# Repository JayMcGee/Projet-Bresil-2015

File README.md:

Projet-Bresil-2015
==================

Projet TSO, Créer une balise avec des capteurs de qualité de l'eau pour l'université de Porto Allegre

http://www.bonebrews.com/temperature-monitoring-with-the-ds18b20-on-a-beaglebone-black/

https://github.com/jlucidar/FabMo-Platform/tree/master/Arch_linux_config/rtl8188CUS-driver-beaglebone

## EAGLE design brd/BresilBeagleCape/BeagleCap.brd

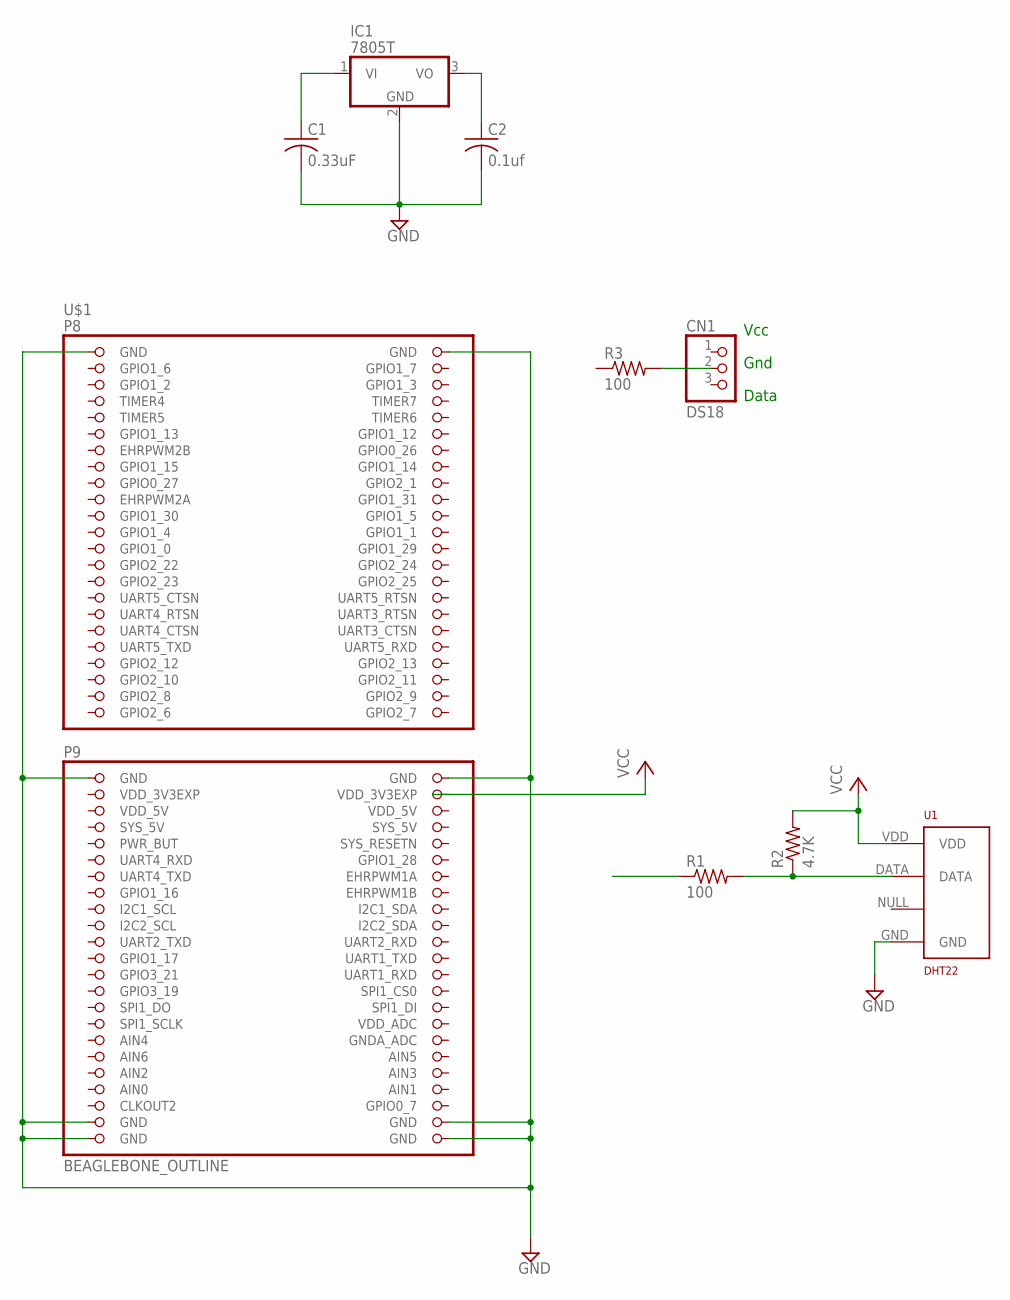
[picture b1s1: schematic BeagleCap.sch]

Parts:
C1: 0.33uF; C050-024X044
C2: 0.1uf; C050-024X044
CN1: DS18; JSTPH3
IC1: 7805T; TO220H
R1, R3: 100; 0207/10
R2: 4.7K; 0207/10
U1: DHT22; RHT03_DHT-22/RA
U$1: BEAGLEBONE_OUTLINE; BEAGLEBONE_SHIELD

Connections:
AIN0: U$1.85 (AIN0)
GND: C1.2, C2.2, IC1.2 (GND), U1.GND, U$1.1 (GND), U$1.2 (GND), U$1.47 (GND), U$1.48 (GND), U$1.89 (GND), U$1.90 (GND), U$1.91 (GND), U$1.92 (GND)
unnamed: C1.1, IC1.1 (VI)
unnamed: C2.1, IC1.3 (VO)
unnamed: R1.2, R2.1, U1.DATA
unnamed: CN1.2, R3.2
SYS_5V: U$1.53 (SYS_5V)
VCC: R2.2, U1.VDD
VDD_3V3EXP: U$1.49 (VDD_3V3EXP), U$1.50 (VDD_3V3EXP)
VDD_5V: U$1.51 (VDD_5V), U$1.52 (VDD_5V)

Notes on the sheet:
Vcc
Gnd
Data

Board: 2 copper layers, 9 parts (0 on the bottom side), 8 nets, no tracks yet.

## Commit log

2014-10-01 Example de MultiThreading pour le beaglebone
2014-10-01 Ajout de tout ce qui était dans mon fork
2014-10-01 Deplacement de la librairie à un endroit désigné
2014-10-01 Ajout des codes et exemples des années précédentes
2014-10-02 Mise a jour du code pour le PIC32MZ, code crée en parallèle avec l'avancement du BeagleBone pour le cas d'un plan de backup
2014-10-02 Ajout du code des annees précédentes
2014-10-02 Corrections pour que ca fonctionne
2014-10-02 Ajout de documentation pour l'installation de l'IDE pour le BeagleBone
2014-10-03 Trie des documentations et suppression de fichiers superflus (ex: Arduino 1.0.4 IDE)
2014-10-03 Modifications pour compatibilité
2014-10-04 Ajout de notes suite a la lecture de la documentation (manuels technoques) des années précédentes et d'un exemple de JSON en provenance du Drive de Mathieu
2014-10-05 Ajout d'un première version de l'installation de Cloud9 IDE sur le beaglebone/Ubuntu sans erreur et fonctionnement comme voulu
2014-10-05 Mise a jour apres test, la procédure est fonctionnelle sur Ubuntu 14.04 64bit
2014-10-08 Ajout de la méthode d'activation de UART5
2014-10-08 Ajout de source pour DHT22
2014-10-08 Ajout de code de base pour le DHt22
2014-10-13 Ajout d'une librairie de test pour le one wire
2014-10-13 Correction, voila la libraire correctment mise a sa place
2014-10-17 Suppression de la doc pour aller dans le Drive
2014-10-18 Ajout du readme que j'ai supprimé + lien vers device tree
2014-10-19 Added OneWire device class files, makes reading OneWire device in device tree easier.
    Follow this tutorial to create device tree :
    http://www.bonebrews.com/temperature-monitoring-with-the-ds18b20-on-a-beaglebone-black/
2014-10-19 Skeleton classe for UART operated devices. Example based on SIM900
2014-10-19 Other modifications to Makefiles
2014-12-03 Ajout du projet de gestion de fichier JSON pour les test (VS2013)
2014-12-03 Ajout du dossier de board avec le projet eagle CAD
2014-12-03 Correction de l'erreur dans les fichier BRD, bon projet pousser
2014-12-03 Ajout de codes manquants
2014-12-03 Ajout de fichier Commun et du backup de la bd aquarius
2014-12-04 Ajout de commun.cpp et commun.h pour le systeme complet. Inclus une fonction qui permet de retourner la date et l'heure selon la constante definie dans commun lui même
